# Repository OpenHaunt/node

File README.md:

<div align="center">

# OpenHaunt Node

**A PoE-powered, modular, network-discoverable I/O node for scare mazes, haunted attractions and escape rooms.**

One cable in. Power and data. Pick a power board for the load, pick an IO board for the effect.

Driven by [**the-pult**](https://github.com/RuegerEvents/the-pult), or by anything else. The protocol is
[open and documented](docs/08-firmware-and-network.md), plain HTTP/JSON, MQTT and sACN.

</div>

---

## The idea

Immersive attractions are full of small, dumb jobs: flicker a ceiling light, trigger a DMX fixture, read a
reed switch on a prop door, light a strip of WS2812s behind a wall panel, cut mains to a fog machine. Today
each of those is solved with a different box, a different power supply and a different protocol.

OpenHaunt Node is a three-board set that gets **power and data from a single Ethernet cable (PoE)**:

| Board | Role |
|---|---|
| **Mainboard** | Always the same. Does the network. |
| **Power board** | Sets the node's power, 12 W to 71 W. Swapping it is how you change PoE class. |
| **IO board** | Carries its own microcontroller and does the actual effect. |

Every node announces itself over mDNS, describes both boards it carries, and speaks HTTP/JSON, MQTT and
Art-Net/sACN. [the-pult](https://github.com/RuegerEvents/the-pult) is the show console built for it: it
discovers, adopts and drives nodes. The protocol is not tied to it, though. It is open and documented, so
Node-RED, QLab, a Python script or any other show-control software can drive a node directly.

## Status

**Prototypes validated and tested.**

Before building the three-board family, a single-board prototype proves the processor, the network, PoE
and the firmware ([D37](docs/10-design-decisions.md)). That prototype, **V0**, carries the mainboard
electronics, an 802.3af PoE module and the IO the first haunt needed: four relays, two PIR inputs, two
WS2812 outputs and audio.

| | |
|---|---|
| **V0.1** | Ordered at JLCPCB on 2026-10-05, brought up and tested ([`test/firmware`](test/firmware/)) |
| **V0.2** | Bring-up fixes and line out. Tested on the bench against [the-pult](https://github.com/RuegerEvents/the-pult) |
| **Firmware** | 0.5.0: discovery, HTTP and MQTT APIs, effects, audio, pixel strips, broker failover |
| **Product boards** | Mainboard, `PWR-BT4` and `IO-LED8` have schematics and layouts in progress |

Decisions D1 to D38 in [10 — Design Decisions](docs/10-design-decisions.md) record what was chosen and why.
Superseded decisions say so at the top of their entry instead of being deleted.

## Headline specifications

| | |
|---|---|
| ⚡ **Power** | IEEE 802.3af, 802.3at or 802.3bt Type 3/4, by power board. **12 W to 71 W** |
| 🔌 **Rails** | Up to 24 V, 12 V and 5 V, each with a hardware eFuse and V/I/W metering. Every board makes its own 3.3 V |
| 🔗 **Connector** | Neutrik NE8FAH-LR-DAE etherCON with Halo light ring, discrete Würth 7490220122 magnetics |
| 🌐 **Network** | 100 Mbit/s Ethernet, W5500 (MAC + PHY) over SPI |
| 🧠 **Host MCU** | ESP32-S3, dual-core 240 MHz, USB host. Wi-Fi stands by as a fallback on V0 |
| 🎛️ **IO MCU** | RP2354, dual-core 150 MHz, 2 MB flash, 12 PIO state machines |
| 🔀 **Board link** | **USB full-speed**, unchanged across generations |
| 💾 **Storage** | 16 MB internal flash (firmware, OTA, assets, IO images) |
| 📡 **Discovery** | mDNS `_openhaunt._tcp`, with both board types and the power budget in TXT records |
| 🛡️ **Isolation** | 1500 V (PoE), plus per-IO-board barriers where needed |

## Repository layout

```
docs/       Concept, architecture, per-board design, protocols, decisions
firmware/   ESP-IDF firmware for every node: one image, the module decides what it is
hardware/   KiCad projects
  OH_Node_V0_Prototype/   single-board prototype, production files, 3D-printed enclosure
  OH_Node_Mainboard/      product mainboard
  OH_Node_PWR_BT4/        802.3bt Type 4 power board
  OH_Node_IO_LED8/        first IO board, RP2354
  tools/                  gnd_reach, return_vias: board analysis scripts
test/       Bring-up firmware for V0.1 (PlatformIO)
```

## Documentation

**Start with 01 and 02.** If you want to know *why* something is the way it is, go straight to
[10 — Design Decisions](docs/10-design-decisions.md). It exists so that settled questions are not reopened.

#### Hardware

| Document | Contents |
|---|---|
| [01 — Product Concept](docs/01-product-concept.md) | What it is, who it's for, why three boards |
| [02 — System Architecture](docs/02-system-architecture.md) | Block diagram, isolation domains, power tree, thermal |
| [03 — Mainboard](docs/03-mainboard.md) | etherCON, magnetics, ESP32-S3, W5500, pin allocation |
| [04 — Power Board](docs/04-power-board.md) | PoE variants, rails, eFuses, metering, identification |
| [05 — IO Board](docs/05-io-board.md) | Why the RP2354 is there, the link, firmware update |
| [06 — Board Interfaces](docs/06-board-interfaces.md) | The three connector contracts, descriptors, boot sequence, mechanics |
| [07 — IO Board Catalog](docs/07-io-board-catalog.md) | Planned IO boards, from DMX to mains switching |
| [09 — Compliance & Safety](docs/09-compliance-and-safety.md) | EMC, SELV, radio approval, the mains problem |
| [12 — V0 Prototype](docs/12-v0-prototype.md) | The single-board prototype as built, and its revisions |

#### Firmware and protocol

| Document | Contents |
|---|---|
| [08 — Firmware & Network](docs/08-firmware-and-network.md) | Two processors, discovery, APIs, protocols, Node-RED |
| [13 — Audio](docs/13-audio.md) | Clips on the node, RTP streams, sound at a stated show time |
| [14 — Pixels](docs/14-pixels.md) | WS2812 strips: effects drawn on the node, or streamed pixels |
| [15 — Brokers](docs/15-brokers.md) | MQTT brokers, and a console that fails over |
| [16 — Standalone Show](docs/16-standalone-show.md) | A show a console puts on a node, which then runs it alone (designed, not built) |

#### Project

| Document | Contents |
|---|---|
| [10 — Design Decisions](docs/10-design-decisions.md) | Why each part was chosen and what was rejected |
| [11 — Open Questions](docs/11-open-questions.md) | What still has to be decided |

## Naming

**OpenHaunt** is the umbrella project. **OpenHaunt Node** is the hardware platform in this repository:
one mainboard, a few power boards, and a growing family of IO boards. Show control is
[the-pult](https://github.com/RuegerEvents/the-pult), which speaks the node protocol of
[08 — Firmware & Network](docs/08-firmware-and-network.md).

## License

Not yet decided. See [11 — Open Questions](docs/11-open-questions.md).

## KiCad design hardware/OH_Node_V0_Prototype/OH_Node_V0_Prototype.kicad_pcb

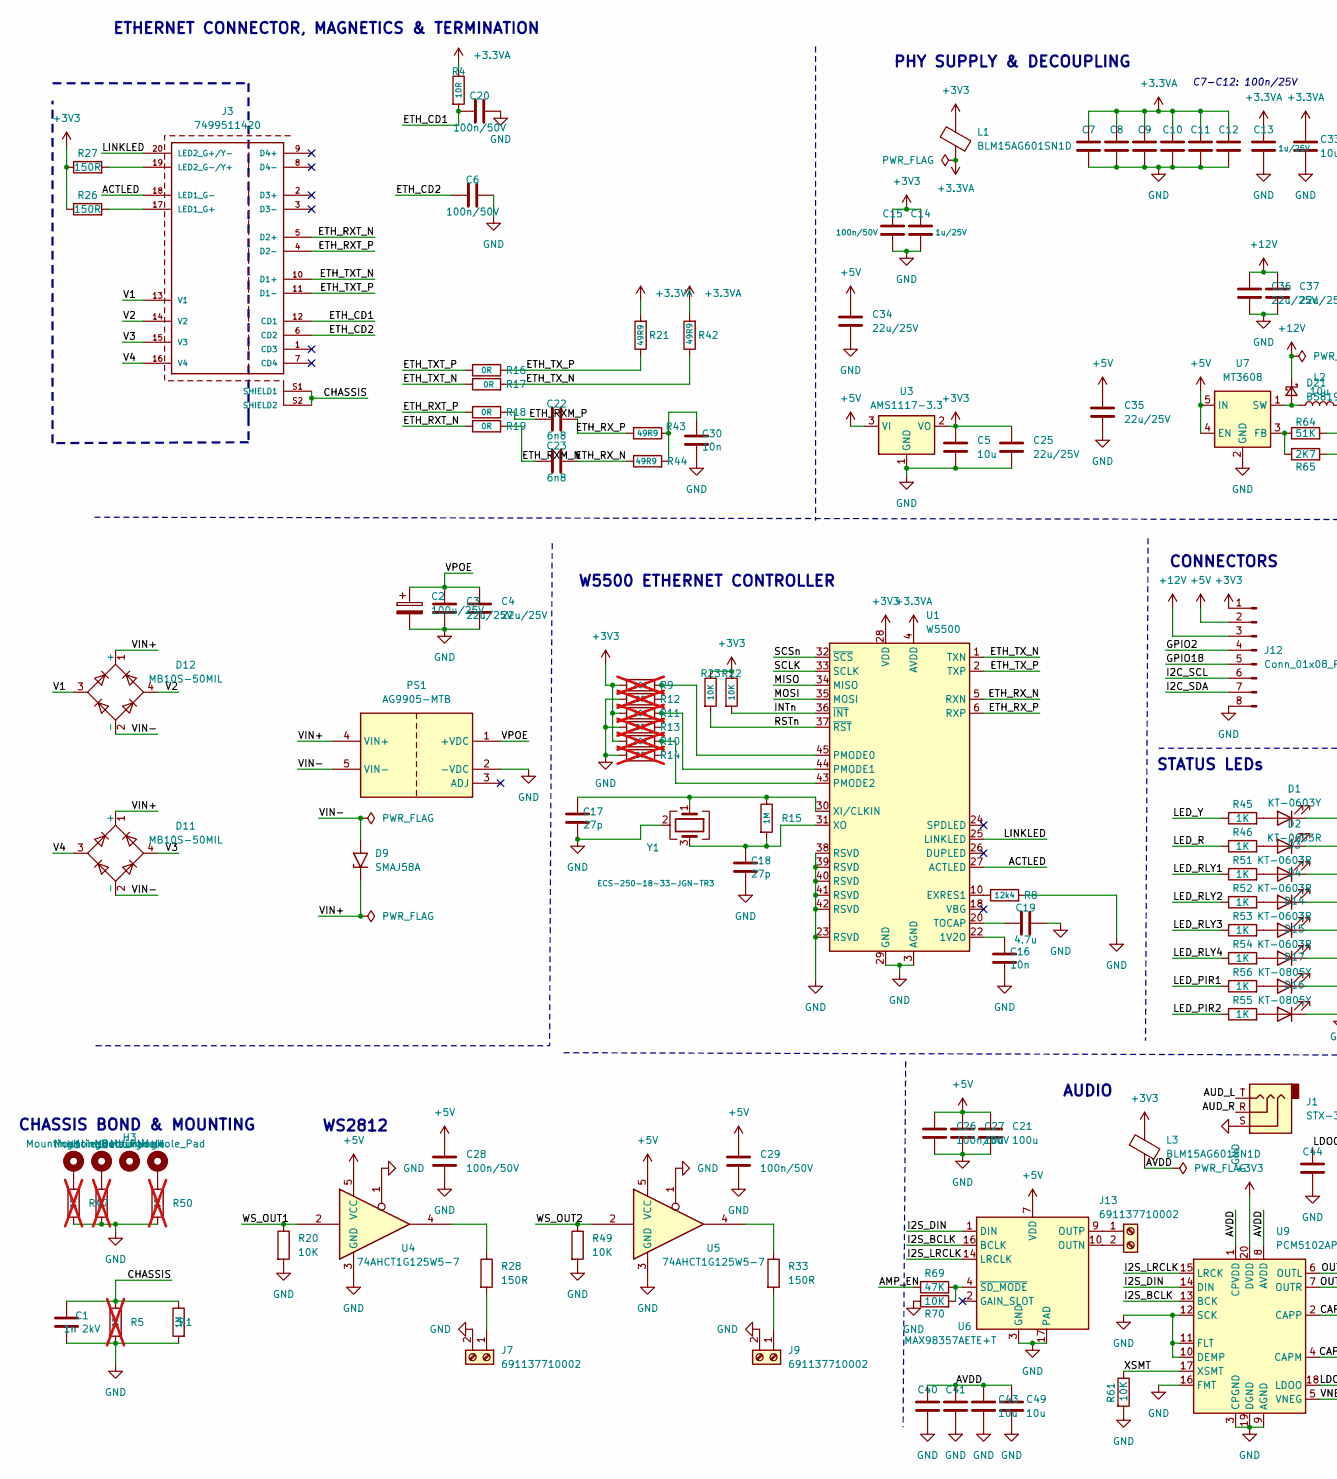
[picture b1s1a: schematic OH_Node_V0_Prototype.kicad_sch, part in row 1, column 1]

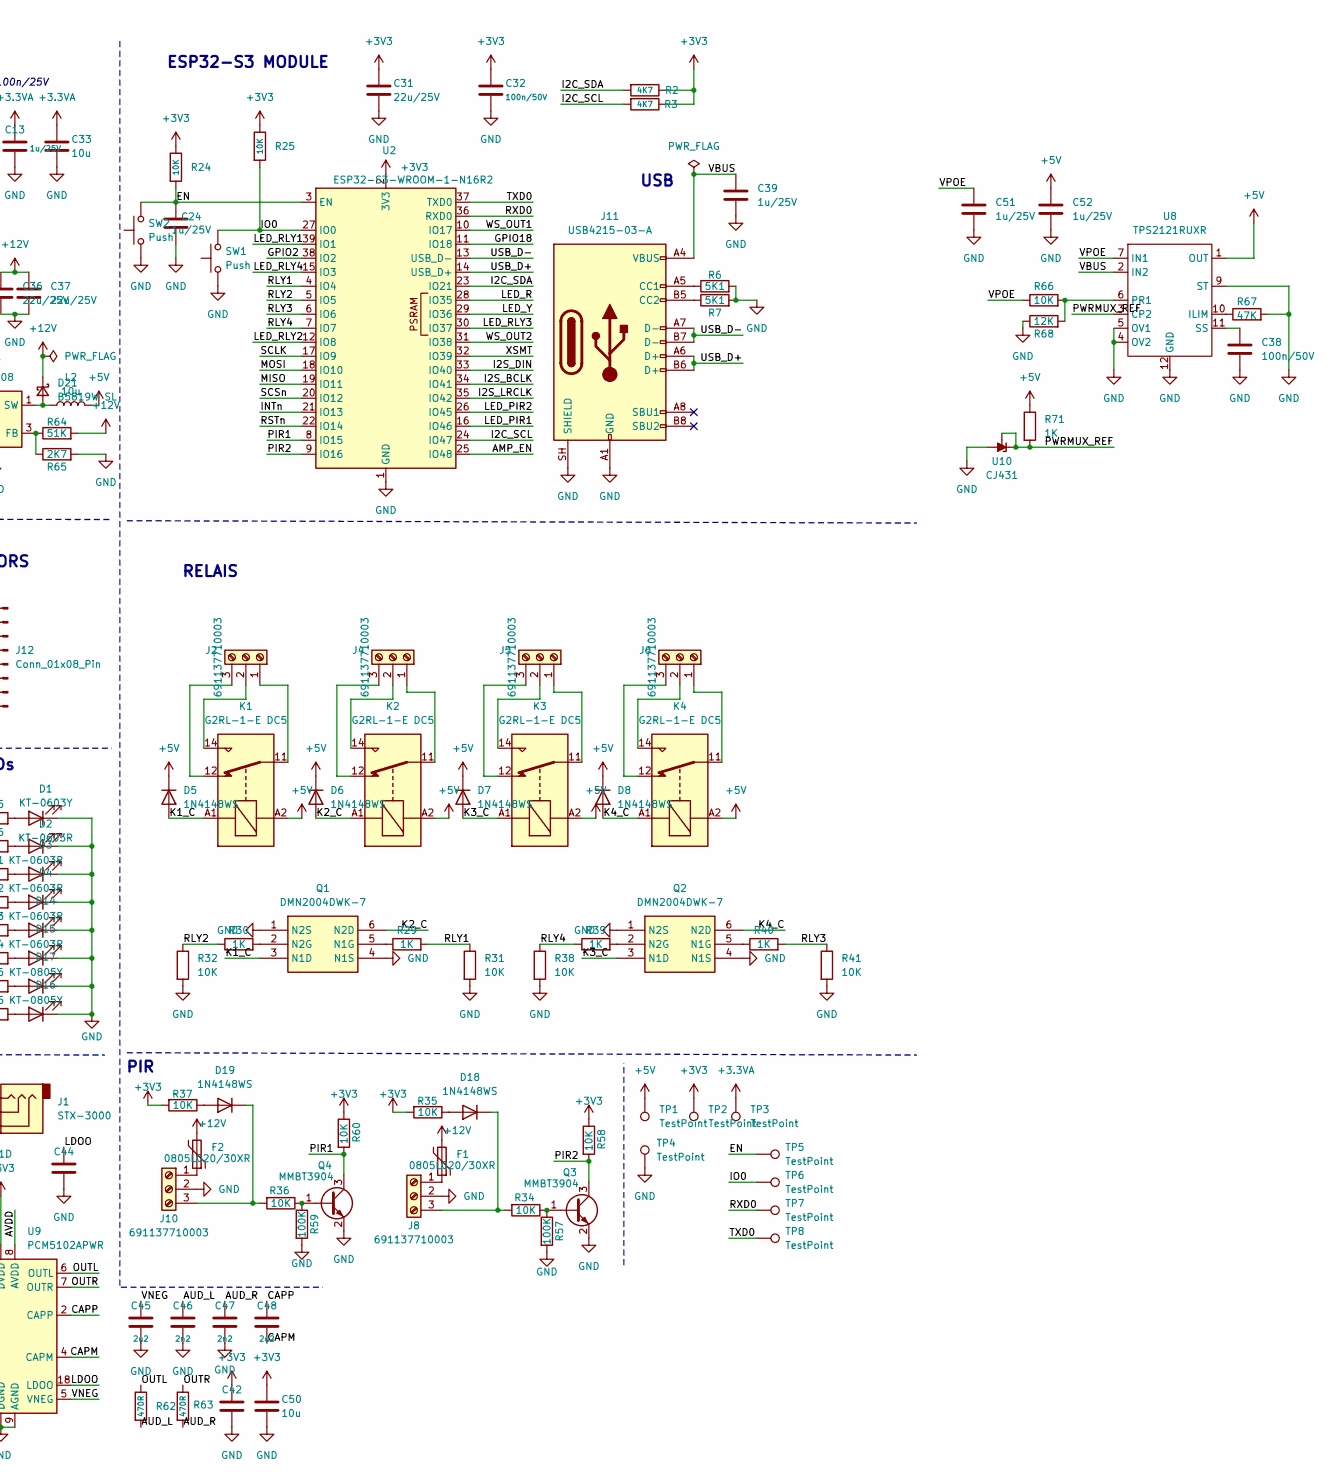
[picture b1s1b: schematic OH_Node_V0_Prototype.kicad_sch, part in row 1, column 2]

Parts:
C1: 1n 2kV; C_1206_3216Metric; MPN 1206B102K202NT
C2: 100u/25V; CP_Elec_6.3x7.7; MPN FP-025ME101M-SAR
C3, C4, C25, C31, C34, C35, C36, C37: 22u/25V; C_0805_2012Metric; MPN CL21A226MAQNNNE
C5, C27, C33, C43, C49, C50: 10u; C_0402_1005Metric; MPN GRM155R61A106ME11D
C6, C7, C8, C9, C10, C11, C12, C15, C20, C26, C28, C29, C32, C38, C40, C41, C42, C44: 100n/50V; C_0402_1005Metric; MPN CL05B104KB54PNC
C13, C14, C24, C39, C51, C52: 1u/25V; C_0402_1005Metric; MPN CL05A105KA5NQNC
C16, C30: 10n; C_0402_1005Metric; MPN CL05B103KB5NNNC
C17, C18: 27p; C_0402_1005Metric; MPN 0402CG270J500NT
C19: 4.7u; C_0805_2012Metric; MPN CL21A475KAQNNNE
C21: 100u; C_1206_3216Metric; MPN GRM31CR61A107MEA8L
C22, C23: 6n8; C_0402_1005Metric; MPN 0402B682K500NT
C45, C48: 2u2; C_0603_1608Metric; MPN CL10A225KO8NNNC
C46, C47: 2n2; C_0402_1005Metric; MPN 0402B222K500NT
D1: KT-0603Y; LED_0603_1608Metric; MPN KT-0603Y
D2, D3, D4, D14, D15: KT-0603R; LED_0603_1608Metric; MPN KT-0603R
D5, D6, D7, D8, D18, D19: 1N4148WS; D_SOD-323; MPN 1N4148WS
D9: SMAJ58A; D_SMA; MPN SMAJ58A
D11, D12: MB10S-50MIL; TO-269AA; MPN MB10S-50MIL
D16, D17: KT-0805Y; LED_0805_2012Metric; MPN KT-0805Y
D21: B5819W SL; D_SOD-123; MPN B5819W SL
F1, F2: 0805L020/30XR; Fuse_0805_2012Metric; MPN 0805L020/30XR
H1, H2, H4: MountingHole_Pad; MountingHole_2.7mm_M2.5_DIN965_Pad
H3: MountingHole; MountingHole_2.7mm_M2.5_DIN965_Pad
J1: STX-3000; Jack_3.5mm_Kycon_STX-3000_Horizontal; MPN STX-3000
J2, J4, J5, J6, J8, J10: 691137710003; WR-TBL_691137710003; MPN 691137710003
J3: 7499511420; WE-RJ45_7499511420; MPN 7499511420
J7, J9, J13: 691137710002; WR-TBL_691137710002; MPN 691137710002
J11: USB4215-03-A; USB_C_Receptacle_GCT_USB4215-xx-A_16P_TopMnt_Horizontal; MPN USB4215-03-A
J12: Conn_01x08_Pin; PinHeader_1x08_P2.54mm_Vertical; MPN 61300811121
K1, K2, K3, K4: G2RL-1-E DC5; Relay_SPDT_Omron_G2RL-1-E; MPN G2RL-1-E DC5
L1, L3: BLM15AG601SN1D; L_0402_1005Metric; MPN BLM15AG601SN1D
L2: 10u; L_Sunlord_SWPA4030S; MPN SWPA4030S100MT
PS1: AG9905-MTB; AG9900-MTB_HandSolder; MPN AG9905-MTB
Q1, Q2: DMN2004DWK-7; SOT-363_SC-70-6; MPN DMN2004DWK-7
Q3, Q4: MMBT3904; SOT-23; MPN MMBT3904
R1: 1M; R_0603_1608Metric; MPN 0603WAF1004T5E
R2, R3: 4K7; R_0402_1005Metric; MPN 0402WGF4701TCE
R4: 10R; R_0402_1005Metric; MPN 0402WGF100JTCE
R5, R12, R13, R14, R47, R48, R50: 0R; R_0402_1005Metric; MPN 0402WGF0000TCE; not fitted
R6, R7: 5K1; R_0402_1005Metric; MPN 0402WGF5101TCE
R8: 12k4; R_0402_1005Metric; MPN 0402WGF1242TCE
R9, R10, R11: 10K; R_0402_1005Metric; MPN 0402WGF1002TCE; not fitted
R15: 1M; R_0402_1005Metric; MPN 0402WGF1004TCE
R16, R17, R18, R19: 0R; R_0402_1005Metric; MPN 0402WGF0000TCE
R20, R22, R23, R24, R25, R31, R32, R34, R35, R36, R37, R38, R41, R49, R58, R60, R61, R66, R70: 10K; R_0402_1005Metric; MPN 0402WGF1002TCE
R21, R42, R43, R44: 49R9; R_0402_1005Metric; MPN 0402WGF499JTCE
R26, R27, R28, R33: 150R; R_0402_1005Metric; MPN 0402WGF1500TCE
R29, R30, R39, R40, R45, R46, R51, R52, R53, R54, R55, R56, R71: 1K; R_0402_1005Metric; MPN 0402WGF1001TCE
R57, R59: 100K; R_0402_1005Metric; MPN 0402WGF1003TCE
R62, R63: 470R; R_0402_1005Metric; MPN 0402WGF4700TCE
R64: 51K; R_0603_1608Metric; MPN 0603WAF5102T5E
R65: 2K7; R_0603_1608Metric; MPN 0603WAF2701T5E
R67, R69: 47K; R_0402_1005Metric; MPN 0402WGF4702TCE
R68: 12K; R_0402_1005Metric; MPN 0402WGF1202TCE
SW1, SW2: Push; SW_Push_1P1T_XKB_TS-1187A; MPN TS-1187A-B-A-B
TP1, TP2, TP3, TP4, TP5, TP6, TP7, TP8: TestPoint; TestPoint_Pad_D1.5mm
U1: W5500; LQFP-48_7x7mm_P0.5mm; MPN W5500
U2: ESP32-S3-WROOM-1-N16R2; Espressif_ESP32-S3-WROOM-1; MPN ESP32-S3-WROOM-1-N16R2
U3: AMS1117-3.3; SOT-223-3_TabPin2; MPN AMS1117-3.3
U4, U5: 74AHCT1G125W5-7; SOT-23-5; MPN 74AHCT1G125W5-7
U6: MAX98357AETE+T; TQFN-16-1EP_3x3mm_P0.5mm_EP1.23x1.23mm; MPN MAX98357AETE+T
U7: MT3608; SOT-23-6; MPN MT3608
U8: TPS2121RUXR; Texas_VQFN-HR-12_2x2.5mm_P0.5mm; MPN TPS2121RUXR
U9: PCM5102APWR; TSSOP-20_4.4x6.5mm_P0.65mm; MPN PCM5102APWR
U10: CJ431; SOT-23; MPN CJ431
Y1: ECS-250-18-33-JGN-TR3; Crystal_SMD_3225-4Pin_3.2x2.5mm; MPN ECS-250-18-33-JGN-TR3

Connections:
+3.3VA: C7.1, C8.1, C9.1, C10.1, C11.1, C12.1, C13.1, C33.1, L1.2, R4.1, R21.2, R42.2, TP3.1 (1_1), U1.4 (AVDD), U1.8 (AVDD), U1.11 (AVDD), U1.15 (AVDD), U1.17 (AVDD), U1.21 (AVDD)
+3V3: C5.1, C14.1, C15.1, C25.1, C31.1, C32.1, C42.1, C50.1, J12.1, L1.1, L3.1, R2.1, R3.1, R9.1, R10.1, R11.1, R22.1, R23.1, R24.1, R25.1, R26.1, R27.1, R35.2, R37.2, R58.1, R60.1, TP2.1 (1_1), U1.28 (VDD), U2.2 (3V3), U3.2 (VO), U9.20 (DVDD)
+5V: C21.1, C26.1, C27.1, C28.1, C29.1, C34.1, C35.1, C52.1, D5.1 (K), D6.1 (K), D7.1 (K), D8.1 (K), J12.2, K1.A2, K2.A2, K3.A2, K4.A2, L2.2, R71.1, TP1.1 (1_1), U3.3 (VI), U4.5 (VCC), U5.5 (VCC), U6.7 (VDD), U6.8 (VDD), U7.4 (EN), U7.5 (IN), U8.1 (OUT), U8.8 (OUT)
+12V: C36.1, C37.1, D21.1 (K), F1.2, F2.2, J12.3, R64.2
/ACTLED: J3.18 (LED1_G-), U1.27 (ACTLED)
/AMP_EN: R69.1, U2.25 (IO48)
/AUD_L: C46.1, J1.T, R62.2
/AUD_R: C47.1, J1.R, R63.2
/AVDD: C40.1, C41.1, C43.1, C49.1, L3.2, U9.1 (CPVDD), U9.8 (AVDD)
/CAPM: C48.2, U9.4 (CAPM)
/CAPP: C48.1, U9.2 (CAPP)
/CHASSIS: C1.1, J3.S1 (SHIELD1), J3.S2 (SHIELD2), R1.1, R5.1
/EN: C24.1, R24.2, SW2.2, TP5.1 (1_1), U2.3 (EN)
/ETH_CD1: C20.1, J3.12 (CD1), R4.2
/ETH_CD2: C6.1, J3.6 (CD2)
/ETH_RXM_N: C23.1, R19.2
/ETH_RXM_P: C22.1, R18.2
/ETH_RXT_N: J3.5 (D2+), R19.1
/ETH_RXT_P: J3.4 (D2-), R18.1
/ETH_RX_N: C23.2, R44.1, U1.5 (RXN)
/ETH_RX_P: C22.2, R43.2, U1.6 (RXP)
/ETH_TXT_N: J3.10 (D1+), R17.1
/ETH_TXT_P: J3.11 (D1-), R16.1
/ETH_TX_N: R17.2, R42.1, U1.1 (TXN)
/ETH_TX_P: R16.2, R21.1, U1.2 (TXP)
/GPIO2: J12.4, U2.38 (IO2)
/GPIO18: J12.5, U2.11 (IO18)
/I2C_SCL: J12.6, R3.2, U2.24 (IO47)
/I2C_SDA: J12.7, R2.2, U2.23 (IO21)
/I2S_BCLK: U2.34 (IO41), U6.16 (BCLK), U9.13 (BCK)
/I2S_DIN: U2.33 (IO40), U6.1 (DIN), U9.14 (DIN)
/I2S_LRCLK: U2.35 (IO42), U6.14 (LRCLK), U9.15 (LRCK)
/INTn: R22.2, U1.36 (~INT), U2.21 (IO13)
/IO0: R25.2, SW1.2, TP6.1 (1_1), U2.27 (IO0)
/K1_C: D5.2 (A), K1.A1, Q1.3 (N1D)
/K2_C: D6.2 (A), K2.A1, Q1.6 (N2D)
/K3_C: D7.2 (A), K3.A1, Q2.3 (N1D)
/K4_C: D8.2 (A), K4.A1, Q2.6 (N2D)
/LDOO: C44.1, U9.18 (LDOO)
/LED_PIR1: R56.1, U2.16 (IO46)
/LED_PIR2: R55.1, U2.26 (IO45)
/LED_R: R46.1, U2.28 (IO35)
/LED_RLY1: R51.1, U2.39 (IO1)
/LED_RLY2: R52.1, U2.12 (IO8)
/LED_RLY3: R53.1, U2.30 (IO37)
/LED_RLY4: R54.1, U2.15 (IO3)
/LED_Y: R45.1, U2.29 (IO36)
/LINKLED: J3.20 (LED2_G+/Y-), U1.25 (LINKLED)
/MISO: U1.34 (MISO), U2.19 (IO11)
/MOSI: U1.35 (MOSI), U2.18 (IO10)
/OUTL: R62.1, U9.6 (OUTL)
/OUTR: R63.1, U9.7 (OUTR)
/PIR1: Q4.3 (C), R60.2, U2.8 (IO15)
/PIR2: Q3.3 (C), R58.2, U2.9 (IO16)
/PWRMUX_REF: R71.2, U8.3 (CP2), U10.1 (REF), U10.2 (K)
/RLY1: R29.2, R31.1, U2.4 (IO4)
/RLY2: R30.1, R32.1, U2.5 (IO5)
/RLY3: R40.2, R41.1, U2.6 (IO6)
/RLY4: R38.1, R39.1, U2.7 (IO7)
/RSTn: R23.2, U1.37 (~RST), U2.22 (IO14)
/RXD0: TP7.1 (1_1), U2.36 (RXD0)
/SCLK: U1.33 (SCLK), U2.17 (IO9)
/SCSn: U1.32 (~SCS), U2.20 (IO12)
/TXD0: TP8.1 (1_1), U2.37 (TXD0)
/USB_D+: J11.A6 (D+), J11.B6 (D+), U2.14 (USB_D+)
/USB_D-: J11.A7 (D-), J11.B7 (D-), U2.13 (USB_D-)
/V1: D12.3, J3.13 (V1)
/V2: D12.4, J3.14 (V2)
/V3: D11.4, J3.15 (V3)
/V4: D11.3, J3.16 (V4)
/VBUS: C39.1, J11.A4 (VBUS), J11.A9 (VBUS), J11.B4 (VBUS), J11.B9 (VBUS), U8.2 (IN2)
/VIN+: D9.1 (A1), D11.1 (+), D12.1 (+), PS1.4 (VIN+)
/VIN-: D9.2 (A2), D11.2 (-), D12.2 (-), PS1.5 (VIN-)
/VNEG: C45.1, U9.5 (VNEG)
/VPOE: C2.1, C3.1, C4.1, C51.1, PS1.1 (+VDC), R66.1, U8.7 (IN1)
/WS_OUT1: R20.1, U2.10 (IO17), U4.2
/WS_OUT2: R49.1, U2.31 (IO38), U5.2
/XSMT: R61.1, U2.32 (IO39), U9.17 (XSMT)
GND: C1.2, C2.2, C3.2, C4.2, C5.2, C6.2, C7.2, C8.2, C9.2, C10.2, C11.2, C12.2, C13.2, C14.2, C15.2, C16.2, C17.2, C18.2, C19.2, C20.2, C21.2, C24.2, C25.2, C26.2, C27.2, C28.2, C29.2, C30.2, C31.2, C32.2, C33.2, C34.2, C35.2, C36.2, C37.2, C38.2, C39.2, C40.2, C41.2, C42.2, C43.2, C44.2, C45.2, C46.2, C47.2, C49.2, C50.2, C51.2, C52.2, D1.1 (K), D2.1 (K), D3.1 (K), D4.1 (K), D14.1 (K), D15.1 (K), D16.1 (K), D17.1 (K), J1.S, J7.2, J8.2, J9.2, J10.2, J11.A1 (GND), J11.A12 (GND), J11.B1 (GND), J11.B12 (GND), J11.SH (SHIELD), J12.8, PS1.2 (-VDC), Q1.1 (N2S), Q1.4 (N1S), Q2.1 (N2S), Q2.4 (N1S), Q3.2 (E), Q4.2 (E), R1.2, R5.2, R6.2, R7.2, R8.2, R12.1, R13.1, R14.1, R20.2, R31.2, R32.2, R38.2, R41.2, R47.2, R48.2, R49.2, R50.2, R57.2, R59.2, R61.2, R65.2, R67.2, R68.1, R70.1, SW1.1, SW2.1, TP4.1 (1_1), U1.3 (AGND), U1.9 (AGND), U1.14 (AGND), U1.16 (AGND), U1.19 (AGND), U1.23 (RSVD), U1.29 (GND), U1.38 (RSVD), U1.39 (RSVD), U1.40 (RSVD), U1.41 (RSVD), U1.42 (RSVD), U1.48 (AGND), U2.1 (GND), U2.40 (GND), U2.41 (GND), U3.1 (GND), U4.1, U4.3 (GND), U5.1, U5.3 (GND), U6.3 (GND), U6.11 (GND), U6.15 (GND), U6.17 (PAD), U7.2 (GND), U8.4 (OV2), U8.5 (OV1), U8.9 (ST), U8.12 (GND), U9.3 (CPGND), U9.9 (AGND), U9.10 (DEMP), U9.11 (FLT), U9.12 (SCK), U9.16 (FMT), U9.19 (DGND), U10.3 (A), Y1.2 (G), Y1.4 (G)
unnamed: C30.1, R43.1, R44.2
unnamed: D1.2 (A), R45.2
unnamed: D2.2 (A), R46.2
unnamed: D3.2 (A), R51.2
unnamed: D4.2 (A), R52.2
unnamed: D14.2 (A), R53.2
unnamed: D15.2 (A), R54.2
unnamed: D16.2 (A), R55.2
unnamed: D17.2 (A), R56.2
unnamed: D18.2 (A), R35.1
unnamed: D18.1 (K), J8.3, R34.2
unnamed: D19.2 (A), R37.1
unnamed: D19.1 (K), J10.3, R36.2
unnamed: D21.2 (A), L2.1, U7.1 (SW)
unnamed: H1.1 (1_1), R47.1
unnamed: H2.1 (1_1), R48.1
unnamed: H4.1 (1_1), R50.1
unnamed: J2.1, K1.11
unnamed: J2.2, K1.14
unnamed: J2.3, K1.12
unnamed: J3.17 (LED1_G+), R26.2
unnamed: J3.19 (LED2_G-/Y+), R27.2
unnamed: J4.1, K2.11
unnamed: J4.2, K2.14
unnamed: J4.3, K2.12
unnamed: J5.1, K3.11
unnamed: J5.2, K3.14
unnamed: J5.3, K3.12
unnamed: J6.1, K4.11
unnamed: J6.2, K4.14
unnamed: J6.3, K4.12
unnamed: J7.1, R28.2
unnamed: F1.1, J8.1
unnamed: J9.1, R33.2
unnamed: F2.1, J10.1
unnamed: J11.A5 (CC1), R6.1
unnamed: J11.B5 (CC2), R7.1
unnamed: J13.1, U6.9 (OUTP)
unnamed: J13.2, U6.10 (OUTN)
unnamed: Q1.5 (N1G), R29.1
unnamed: Q1.2 (N2G), R30.2
unnamed: Q2.5 (N1G), R40.1
unnamed: Q2.2 (N2G), R39.2
unnamed: Q3.1 (B), R34.1, R57.1
unnamed: Q4.1 (B), R36.1, R59.1
unnamed: R28.1, U4.4
unnamed: R33.1, U5.4
unnamed: C16.1, U1.22 (1V2O)
unnamed: R8.1, U1.10 (EXRES1)
unnamed: R9.2, R12.2, U1.45 (PMODE0)
unnamed: R11.2, R13.2, U1.44 (PMODE1)
unnamed: R10.2, R14.2, U1.43 (PMODE2)
unnamed: C19.1, U1.20 (TOCAP)
unnamed: C17.1, R15.1, U1.30 (XI/CLKIN), Y1.1
unnamed: C18.1, R15.2, U1.31 (XO), Y1.3
unnamed: R69.2, R70.2, U6.4 (~SD_MODE)
unnamed: R64.1, R65.1, U7.3 (FB)
unnamed: R67.1, U8.10 (ILIM)
unnamed: R66.2, R68.2, U8.6 (PR1)
unnamed: C38.1, U8.11 (SS)

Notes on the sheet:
C7-C12: 100n/25V
ETHERNET CONNECTOR, MAGNETICS & TERMINATION
PIR
USB
ESP32-S3 MODULE
PHY SUPPLY & DECOUPLING
AUDIO
RELAIS
W5500 ETHERNET CONTROLLER
CONNECTORS
WS2812
CHASSIS BOND & MOUNTING
STATUS LEDs

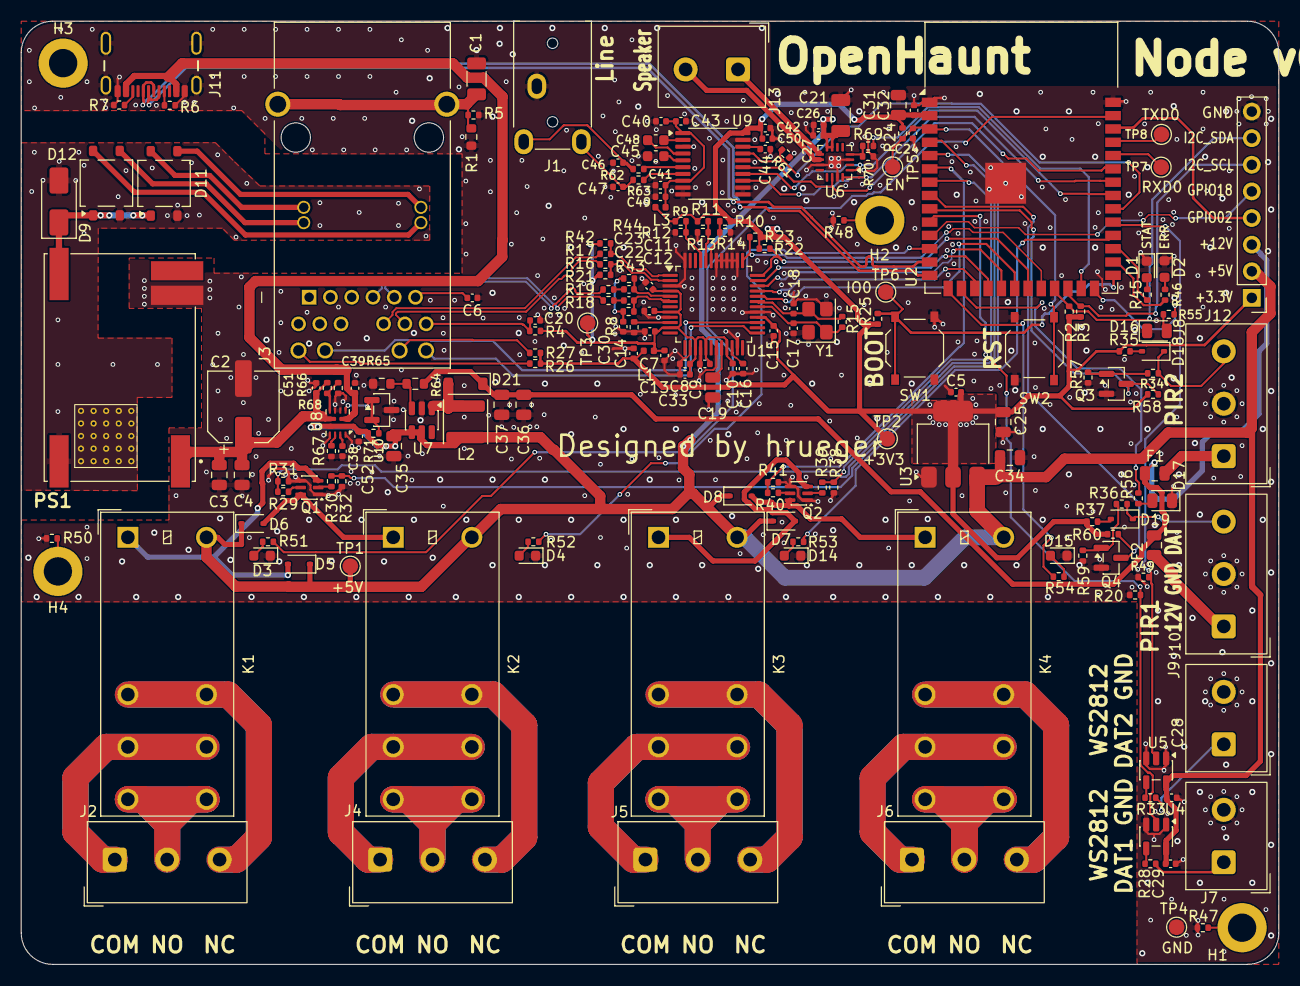
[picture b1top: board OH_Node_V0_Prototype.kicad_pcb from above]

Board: 4 copper layers, 120.0 x 90.0 mm, 193 parts (0 on the bottom side), 139 nets.

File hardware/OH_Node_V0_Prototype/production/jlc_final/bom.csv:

Comment,Designator,Footprint,LCSC Part #,MPN
1n 2kV,C1,C_1206_3216Metric,C9196,1206B102K202NT
100u/25V,C2,CP_Elec_6.3x7.7,C50146718,FP-025ME101M-SAR
22u/25V,"C3,C4,C25,C31,C34,C35,C36,C37",C_0805_2012Metric,C45783,CL21A226MAQNNNE
10u,"C5,C27,C33,C43,C49,C50",C_0402_1005Metric,C408132,GRM155R61A106ME11D
100n/50V,"C6,C7,C8,C9,C10,C11,C12,C15,C20,C26,C28,C29,C32,C38,C40,C41,C42,C44",C_0402_1005Metric,C307331,CL05B104KB54PNC
1u/25V,"C13,C14,C24,C39,C51,C52",C_0402_1005Metric,C52923,CL05A105KA5NQNC
10n,"C16,C30",C_0402_1005Metric,C15195,CL05B103KB5NNNC
27p,"C17,C18",C_0402_1005Metric,C1557,0402CG270J500NT
4.7u,C19,C_0805_2012Metric,C1779,CL21A475KAQNNNE
100u,C21,C_1206_3216Metric,C883598,GRM31CR61A107MEA8L
6n8,"C22,C23",C_0402_1005Metric,C1542,0402B682K500NT
2u2,"C45,C48",C_0603_1608Metric,C23630,CL10A225KO8NNNC
2n2,"C46,C47",C_0402_1005Metric,C1531,0402B222K500NT
KT-0603Y,D1,LED_0603_1608Metric,C2287,KT-0603Y
KT-0603R,"D2,D3,D4,D14,D15",LED_0603_1608Metric,C2286,KT-0603R
1N4148WS,"D5,D6,D7,D8,D18,D19",D_SOD-323,C2128,1N4148WS
SMAJ58A,D9,D_SMA,C19077554,SMAJ58A
MB10S-50MIL,"D11,D12",TO-269AA,C2488,MB10S-50MIL
KT-0805Y,"D16,D17",LED_0805_2012Metric,C2296,KT-0805Y
B5819W SL,D21,D_SOD-123,C8598,B5819W SL
0805L020/30XR,"F1,F2",Fuse_0805_2012Metric,C7472560,0805L020/30XR
USB4215-03-A,J11,USB_C_Receptacle_GCT_USB4215-xx-A_16P_TopMnt_Horizontal,C37616412,USB4215-03-A
BLM15AG601SN1D,"L1,L3",L_0402_1005Metric,C76884,BLM15AG601SN1D
10u,L2,L_Sunlord_SWPA4030S,C38117,SWPA4030S100MT
DMN2004DWK-7,"Q1,Q2",SOT-363_SC-70-6,C156343,DMN2004DWK-7
MMBT3904,"Q3,Q4",SOT-23,C20526,MMBT3904
1M,R1,R_0603_1608Metric,C22935,0603WAF1004T5E
4K7,"R2,R3",R_0402_1005Metric,C25900,0402WGF4701TCE
10R,R4,R_0402_1005Metric,C25077,0402WGF100JTCE
5K1,"R6,R7",R_0402_1005Metric,C25905,0402WGF5101TCE
12k4,R8,R_0402_1005Metric,C11692,0402WGF1242TCE
1M,R15,R_0402_1005Metric,C26083,0402WGF1004TCE
0R,"R16,R17,R18,R19",R_0402_1005Metric,C17168,0402WGF0000TCE
10K,"R20,R22,R23,R24,R25,R31,R32,R34,R35,R36,R37,R38,R41,R49,R58,R60,R61,R66,R70",R_0402_1005Metric,C25744,0402WGF1002TCE
49R9,"R21,R42,R43,R44",R_0402_1005Metric,C25120,0402WGF499JTCE
150R,"R26,R27,R28,R33",R_0402_1005Metric,C25082,0402WGF1500TCE
1K,"R29,R30,R39,R40,R45,R46,R51,R52,R53,R54,R55,R56,R71",R_0402_1005Metric,C11702,0402WGF1001TCE
100K,"R57,R59",R_0402_1005Metric,C25741,0402WGF1003TCE
470R,"R62,R63",R_0402_1005Metric,C25117,0402WGF4700TCE
51K,R64,R_0603_1608Metric,C23196,0603WAF5102T5E
2K7,R65,R_0603_1608Metric,C13167,0603WAF2701T5E
47K,"R67,R69",R_0402_1005Metric,C25792,0402WGF4702TCE
12K,R68,R_0402_1005Metric,C25752,0402WGF1202TCE
Push,"SW1,SW2",SW_Push_1P1T_XKB_TS-1187A,C318884,TS-1187A-B-A-B
W5500,U1,LQFP-48_7x7mm_P0.5mm,C32843,W5500
ESP32-S3-WROOM-1-N16R2,U2,Espressif_ESP32-S3-WROOM-1,C2913205,ESP32-S3-WROOM-1-N16R2
AMS1117-3.3,U3,SOT-223-3_TabPin2,C347222,AMS1117-3.3
74AHCT1G125W5-7,"U4,U5",SOT-23-5,C842287,74AHCT1G125W5-7
MAX98357AETE+T,U6,TQFN-16-1EP_3x3mm_P0.5mm_EP1.23x1.23mm,C910544,MAX98357AETE+T
MT3608,U7,SOT-23-6,C84817,MT3608
TPS2121RUXR,U8,Texas_VQFN-HR-12_2x2.5mm_P0.5mm,C485916,TPS2121RUXR
PCM5102APWR,U9,TSSOP-20_4.4x6.5mm_P0.65mm,C107671,PCM5102APWR
CJ431,U10,SOT-23,C3113,CJ431
ECS-250-18-33-JGN-TR3,Y1,Crystal_SMD_3225-4Pin_3.2x2.5mm,C5354421,ECS-250-18-33-JGN-TR3

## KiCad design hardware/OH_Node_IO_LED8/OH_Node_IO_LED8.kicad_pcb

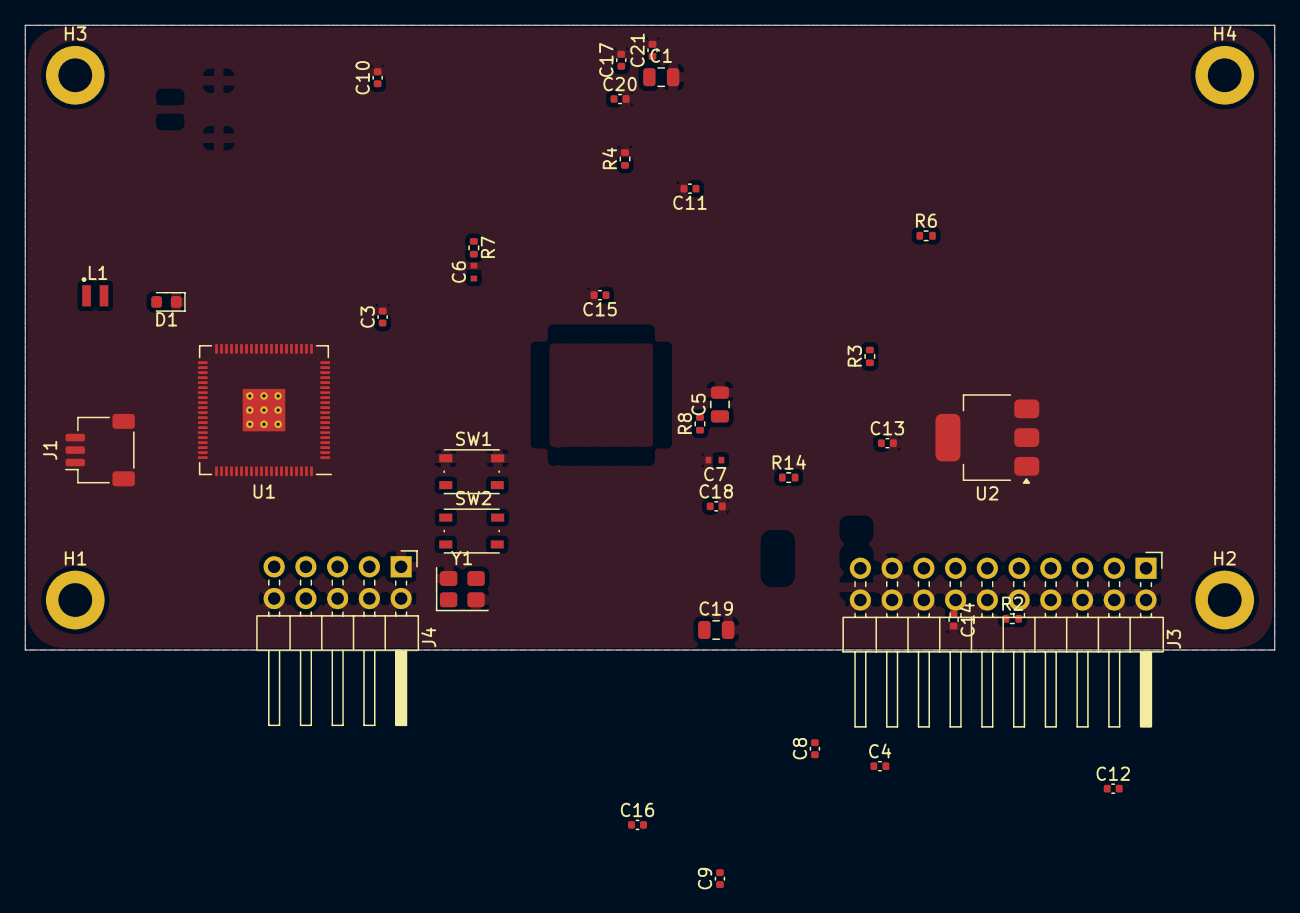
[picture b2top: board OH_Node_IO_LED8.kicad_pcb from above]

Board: 4 copper layers, 100.0 x 50.0 mm, 41 parts (0 on the bottom side), 23 nets, no tracks yet.

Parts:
C1, C5: 22u; C_0805_2012Metric
C3, C4: 15p; C_0402_1005Metric
C6, C7: 4u7; C_0402_1005Metric_small_pads
C8, C11, C12, C13, C14, C15, C16, C17, C18, C20, C21: 100n; C_0402_1005Metric
C9, C10: 4u7; C_0402_1005Metric
C19: 10u; C_0805_2012Metric
D1: Blue Indicator LED; LED_0603_1608Metric
H1, H2, H3, H4: MountingHole; MountingHole_2.7mm_M2.5_DIN965_Pad
J1: SM03B-SRSS-TB; JST_SH_SM03B-SRSS-TB_1x03-1MP_P1.00mm_Horizontal
J3: 61302021021; PinHeader_2x10_P2.54mm_Horizontal
J4: 61301021021; PinHeader_2x05_P2.54mm_Horizontal
L1: 3u3; L_2016_pol
R2, R4, R6: 1K; R_0402_1005Metric
R3: 33; R_0402_1005Metric
R7, R8: 27; R_0402_1005Metric
R14: 110; R_0402_1005Metric
SW1, SW2: Push; SW_Push_1P1T_NO_Vertical_Wuerth_434133025816
U1: RP2354B; RP235XB
U2: AMS1117-3.3; SOT-223-3_TabPin2
Y1: ABM8-272-T3; Crystal_SMD_3225-4Pin_3.2x2.5mm

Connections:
+1V1: C7.1, C8.1, C10.1, C11.1, L1.1, U1.10 (DVDD), U1.32 (DVDD), U1.51 (DVDD), U1.65 (VREG_FB)
+3V3: C5.1, C6.1, C12.1, C13.1, C14.1, C15.1, C16.1, C17.1, C18.1, C19.1, C20.1, C21.1, J3.15, R3.1, U1.5 (IOVDD), U1.15 (IOVDD), U1.24 (IOVDD), U1.29 (IOVDD), U1.41 (IOVDD), U1.50 (IOVDD), U1.59 (ADC_AVDD), U1.60 (IOVDD), U1.64 (VREG_VIN), U1.68 (USB_OTP_VDD), U1.69 (QSPI_IOVDD), U1.76 (IOVDD), U2.2 (VO)
+5V: J3.7, J3.9, J3.11, J3.13
+12V: J3.3, J3.5
/IO_ATTN: J4.8, R6.2, SW1.2
/IO_BOOTSEL: J4.9, U1.48 (GPIO39)
/IO_nRESET: J4.7, SW2.2, U1.35 (RUN)
/RP2354B/QSPI_SS: R6.1, U1.75 (QSPI_SS)
/RP2354B/SWCLK: J1.1, U1.33 (SWCLK)
/RP2354B/SWD: J1.3, U1.34 (SWD)
/RP2354B/VREG_AVDD: C9.1, R3.2, U1.61 (VREG_AVDD)
/RP2354B/VREG_LX: L1.2, U1.63 (VREG_LX)
/RP2354B/XIN: C3.1, U1.30 (XIN), Y1.1
/RP2354B/XOUT: R2.1, U1.31 (XOUT)
/USB_D+: J4.5, R7.1
/USB_D-: J4.3, R8.1
GND: C1.2, C3.2, C4.2, C5.2, C6.2, C7.2, C8.2, C9.2, C10.2, C11.2, C12.2, C13.2, C14.2, C15.2, C16.2, C17.2, C18.2, C19.2, C20.2, C21.2, D1.1 (K), J1.2, J1.MP (MountPin), J3.2, J3.4, J3.6, J3.8, J3.10, J3.12, J3.14, J3.16, J3.17, J3.18, J3.19, J3.20, J4.1, J4.2, J4.4, J4.6, J4.10, R4.2, SW1.1, U1.62 (VREG_PGND), U1.81 (GND), U2.1 (GND), Y1.2, Y1.4
unnamed: C4.1, R2.2, Y1.3
unnamed: D1.2 (A), R14.2
unnamed: R4.1, SW2.1
unnamed: R8.2, U1.66 (USB_DM)
unnamed: R7.2, U1.67 (USB_DP)
VBUS: C1.1, U2.3 (VI)
